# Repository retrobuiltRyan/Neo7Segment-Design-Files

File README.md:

KiCAD 8.x files created.

A reworked layout of Unexpected Maker's 7SegNeo Display project. Chain these addressable LED modules together to make a large 7-segment display. Control via any micro-controller just like you would control a strip of RGB LEDs. Custom library made by Unexpected Maker.

Assembly Required:
Each moduled has a resistor footprint at the Data In line. The first module in the chain requires a ~220-330 ohm resistor soldered here. Each moduled next in the chain requires this jumper closed; 0-ohm resistor or just a solder blob.

Change list: bumped-up passives footprint to 1206, finessed trace/ copper pour layout; slightly larger PCB area, larger mounting holes, decimal place pixel same footprint as all other pixels.
Created some 3D printable mounting brackets to expidite building projects like a clock/scoreboard. 

RGBLEDs: 1568-16347CT-ND or https://www.aliexpress.us/item/3256802466699315.html

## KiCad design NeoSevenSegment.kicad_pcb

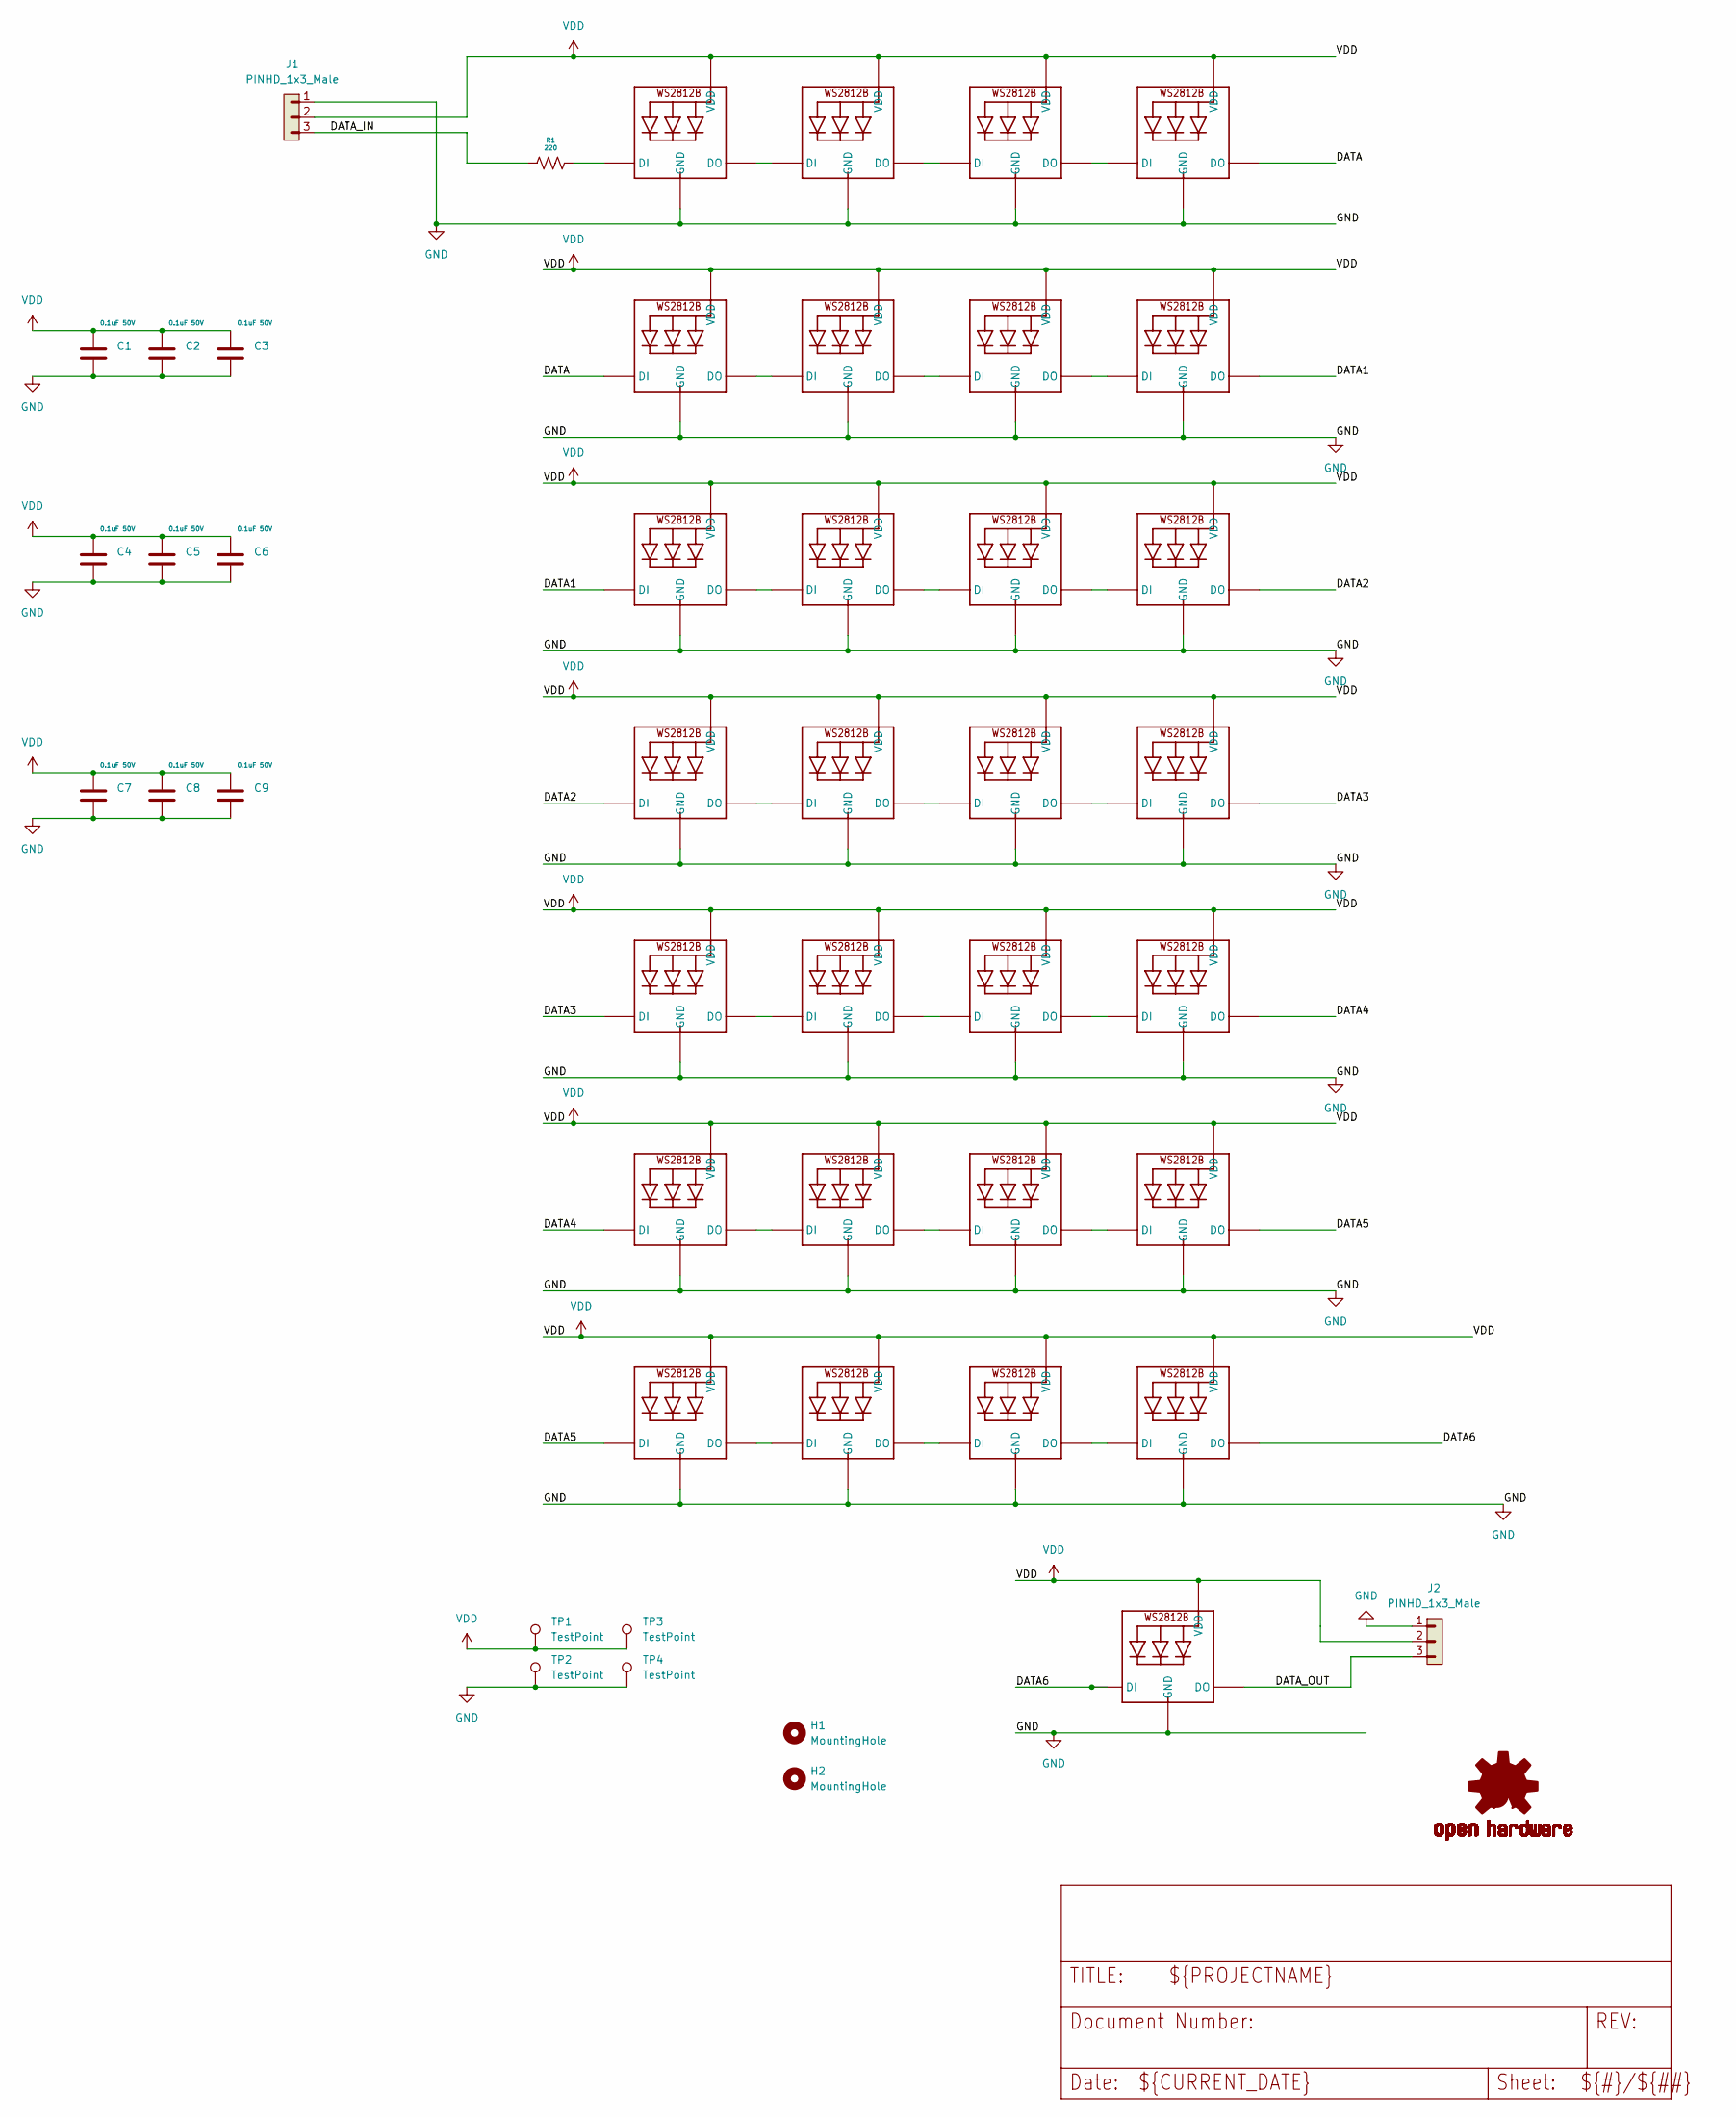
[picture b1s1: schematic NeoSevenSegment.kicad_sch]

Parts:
C1, C2, C3, C4, C5, C6, C7, C8, C9: 0.1uF 50V; C_1206_3216Metric; DigiKey P/N 1276-1068-1-ND
H1, H2: MountingHole; MountingHole_3.2mm_M3_ISO14580_Pad_TopBottom
J1, J2: PINHD_1x3_Male; PinHeader_1x03_P2.54mm_Vertical
LED1, LED2, LED3, LED4, LED5, LED6, LED7, LED8, LED9, LED10, LED11, LED12, LED13, LED14, LED15, LED16, LED17, LED18, LED19, LED20, LED21, LED22, LED23, LED24, LED25, LED26, LED27, LED28, LED29: WS2812B_5050N; WS2812B-NARROW
LOGO1: OSHW-LOGOM; OSHW-LOGO-M
R1: 220; R_1206_3216Metric; DigiKey P/N 311-220FRCT-ND
TP1, TP2, TP3, TP4: TestPoint; TestPoint_Pad_2.5x2.5mm

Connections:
/DATA: LED4.2-DOUT (DO), LED5.4-DIN (DI)
/DATA1: LED8.2-DOUT (DO), LED9.4-DIN (DI)
/DATA2: LED12.2-DOUT (DO), LED13.4-DIN (DI)
/DATA3: LED16.2-DOUT (DO), LED17.4-DIN (DI)
/DATA4: LED20.2-DOUT (DO), LED21.4-DIN (DI)
/DATA5: LED24.2-DOUT (DO), LED25.4-DIN (DI)
/DATA6: LED28.2-DOUT (DO), LED29.4-DIN (DI)
/DATA_IN: J1.3, R1.2
/DATA_OUT: J2.3, LED29.2-DOUT (DO)
GND: C1.2, C2.2, C3.2, C4.2, C5.2, C6.2, C7.2, C8.2, C9.2, J1.1, J2.1, LED1.3-GND (GND), LED2.3-GND (GND), LED3.3-GND (GND), LED4.3-GND (GND), LED5.3-GND (GND), LED6.3-GND (GND), LED7.3-GND (GND), LED8.3-GND (GND), LED9.3-GND (GND), LED10.3-GND (GND), LED11.3-GND (GND), LED12.3-GND (GND), LED13.3-GND (GND), LED14.3-GND (GND), LED15.3-GND (GND), LED16.3-GND (GND), LED17.3-GND (GND), LED18.3-GND (GND), LED19.3-GND (GND), LED20.3-GND (GND), LED21.3-GND (GND), LED22.3-GND (GND), LED23.3-GND (GND), LED24.3-GND (GND), LED25.3-GND (GND), LED26.3-GND (GND), LED27.3-GND (GND), LED28.3-GND (GND), LED29.3-GND (GND), TP2.1, TP4.1
unnamed: LED1.4-DIN (DI), R1.1
unnamed: LED1.2-DOUT (DO), LED2.4-DIN (DI)
unnamed: LED2.2-DOUT (DO), LED3.4-DIN (DI)
unnamed: LED3.2-DOUT (DO), LED4.4-DIN (DI)
unnamed: LED5.2-DOUT (DO), LED6.4-DIN (DI)
unnamed: LED6.2-DOUT (DO), LED7.4-DIN (DI)
unnamed: LED7.2-DOUT (DO), LED8.4-DIN (DI)
unnamed: LED9.2-DOUT (DO), LED10.4-DIN (DI)
unnamed: LED10.2-DOUT (DO), LED11.4-DIN (DI)
unnamed: LED11.2-DOUT (DO), LED12.4-DIN (DI)
unnamed: LED13.2-DOUT (DO), LED14.4-DIN (DI)
unnamed: LED14.2-DOUT (DO), LED15.4-DIN (DI)
unnamed: LED15.2-DOUT (DO), LED16.4-DIN (DI)
unnamed: LED17.2-DOUT (DO), LED18.4-DIN (DI)
unnamed: LED18.2-DOUT (DO), LED19.4-DIN (DI)
unnamed: LED19.2-DOUT (DO), LED20.4-DIN (DI)
unnamed: LED21.2-DOUT (DO), LED22.4-DIN (DI)
unnamed: LED22.2-DOUT (DO), LED23.4-DIN (DI)
unnamed: LED23.2-DOUT (DO), LED24.4-DIN (DI)
unnamed: LED25.2-DOUT (DO), LED26.4-DIN (DI)
unnamed: LED26.2-DOUT (DO), LED27.4-DIN (DI)
unnamed: LED27.2-DOUT (DO), LED28.4-DIN (DI)
VDD: C1.1, C2.1, C3.1, C4.1, C5.1, C6.1, C7.1, C8.1, C9.1, J1.2, J2.2, LED1.1-VDD (VDD), LED2.1-VDD (VDD), LED3.1-VDD (VDD), LED4.1-VDD (VDD), LED5.1-VDD (VDD), LED6.1-VDD (VDD), LED7.1-VDD (VDD), LED8.1-VDD (VDD), LED9.1-VDD (VDD), LED10.1-VDD (VDD), LED11.1-VDD (VDD), LED12.1-VDD (VDD), LED13.1-VDD (VDD), LED14.1-VDD (VDD), LED15.1-VDD (VDD), LED16.1-VDD (VDD), LED17.1-VDD (VDD), LED18.1-VDD (VDD), LED19.1-VDD (VDD), LED20.1-VDD (VDD), LED21.1-VDD (VDD), LED22.1-VDD (VDD), LED23.1-VDD (VDD), LED24.1-VDD (VDD), LED25.1-VDD (VDD), LED26.1-VDD (VDD), LED27.1-VDD (VDD), LED28.1-VDD (VDD), LED29.1-VDD (VDD), TP1.1, TP3.1

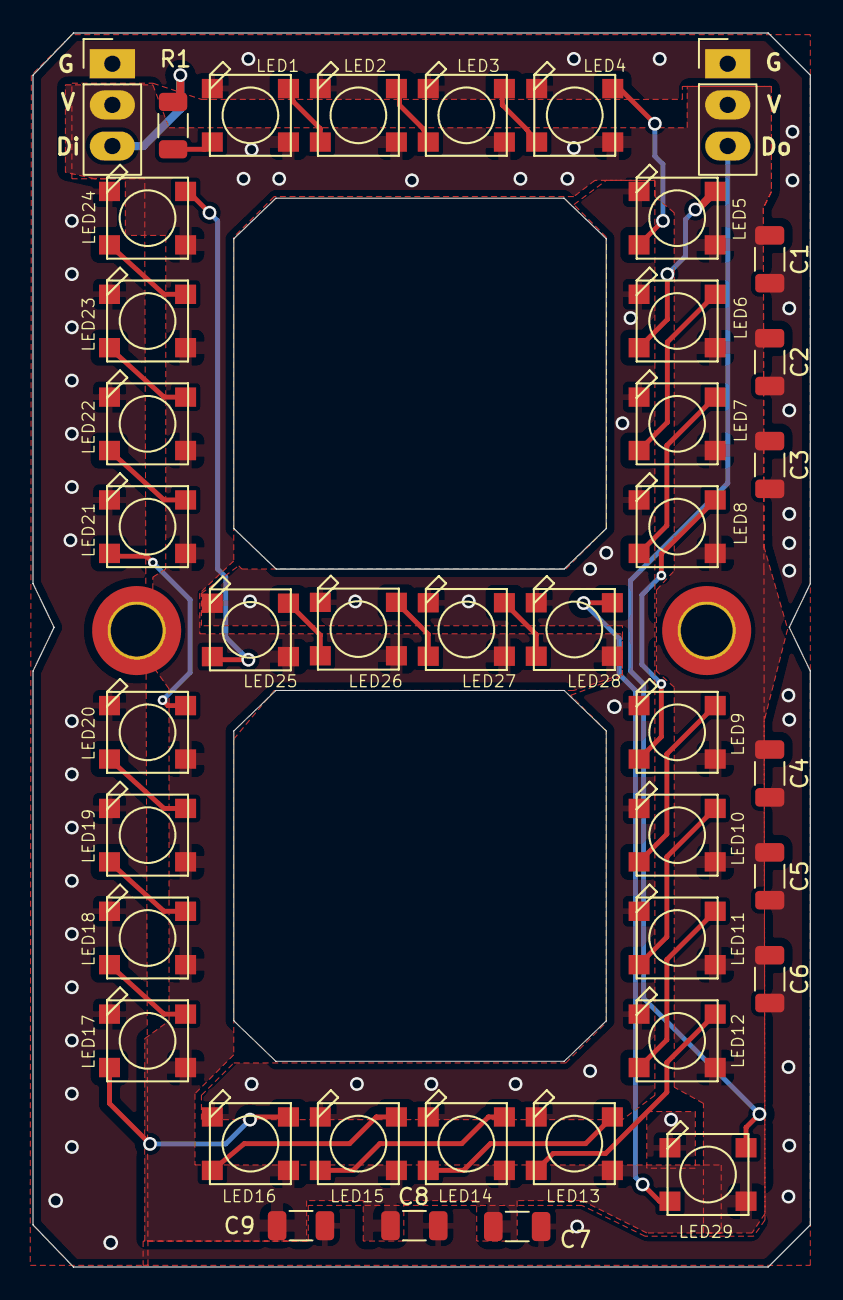
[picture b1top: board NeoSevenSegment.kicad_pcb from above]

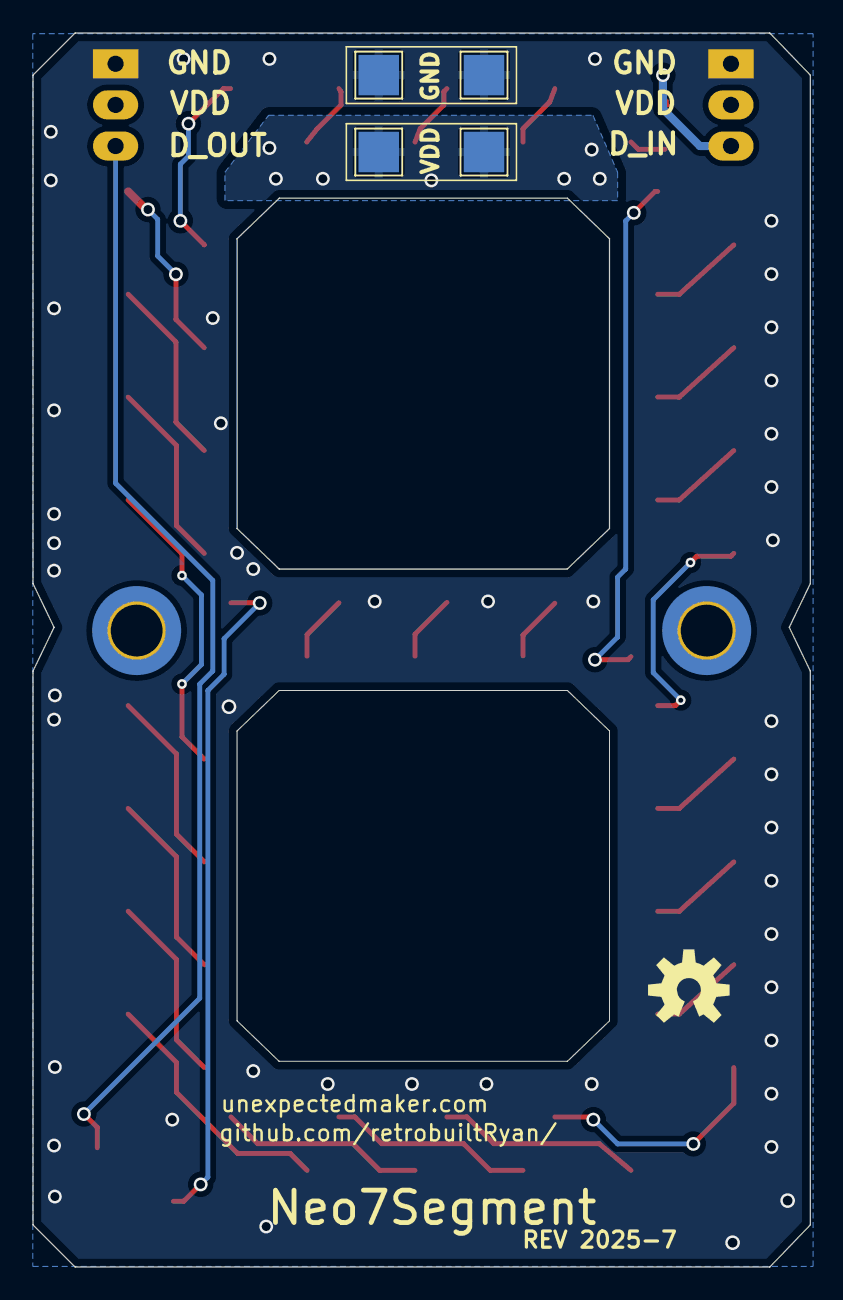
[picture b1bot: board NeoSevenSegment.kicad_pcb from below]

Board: 2 copper layers, 48.0 x 76.2 mm, 48 parts (5 on the bottom side), 33 nets.

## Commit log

2024-11-17 Eagle Design Files and Gerbers (ver Dec 2023)
2025-07-30 design Files
    July 2025 revision. big copper pours for VDD and GND.
2025-07-30 gerbers
2025-10-16 design Files
2025-10-16 gerbers
    JLCPCB tested
2025-10-17 Create LICENSE
